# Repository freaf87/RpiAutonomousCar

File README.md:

Rpi Autonomous Car PCB 
====================
This board bring those additional functions below to the Raspberry pi:

	 - Analog Digital Converter with MCP3008 (8)
	 - DC Brushed Motor driver (2) with TB6612FNG
	 - Level converted IOs (5V <-> 3.3V) (8)
     - 16-channel, 12-bit PWM with PCA9685
     - RGB LED (1)
     - Pushbutton (1)

Top                                                                      |  Bottom
:-----------------------------------------------------------------------:|:--------------------------------------------------------------:
  |  

Author: Frederic Afadjigla, 2018

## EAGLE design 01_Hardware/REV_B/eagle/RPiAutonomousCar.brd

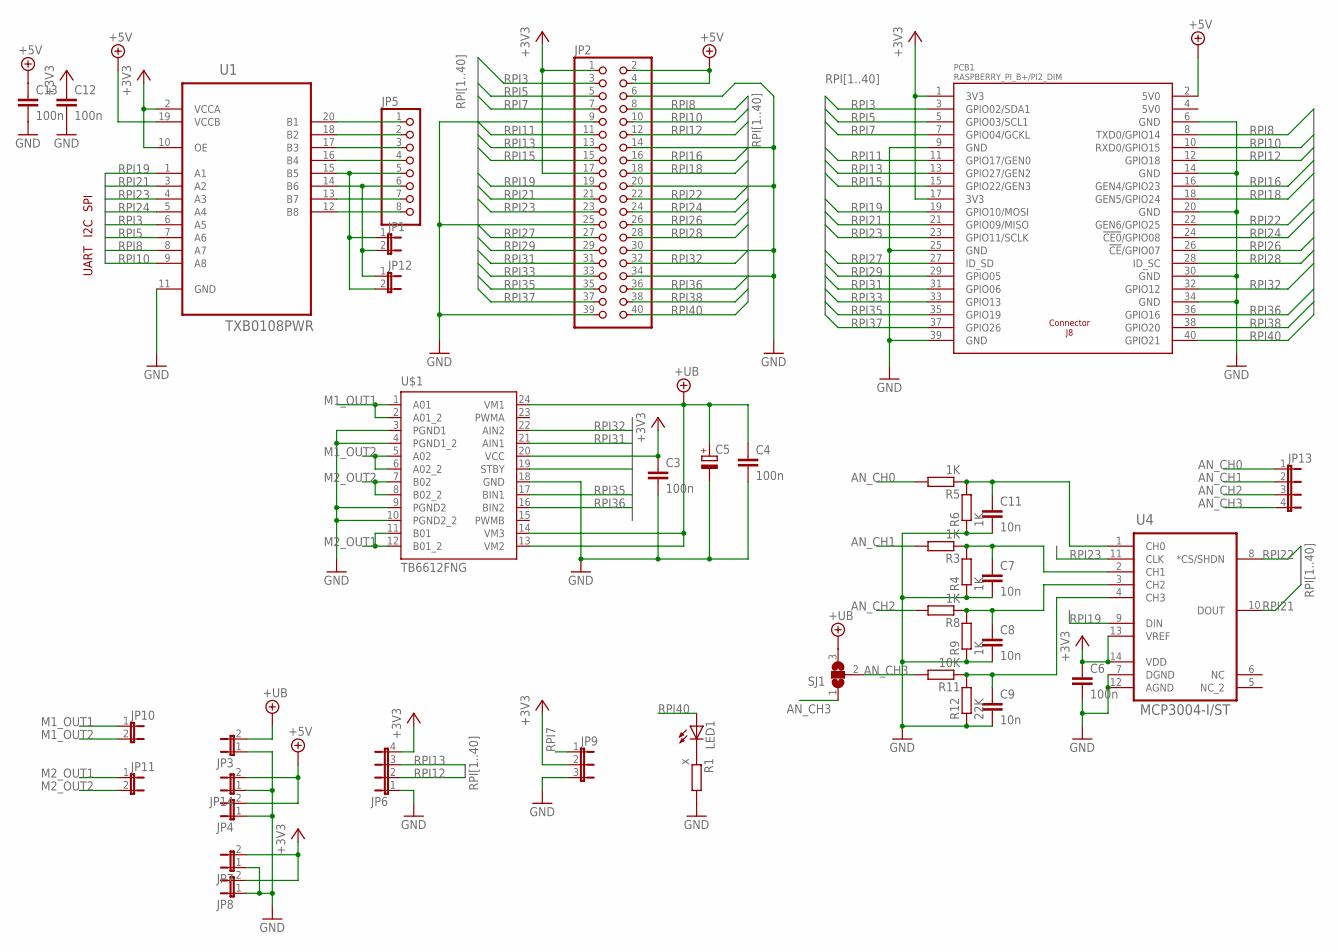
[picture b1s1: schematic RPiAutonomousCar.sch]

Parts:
C3, C4, C6, C12, C13: 100n; C0603
C5: CPOL-EU153CLV-0405; 153CLV-0405
C7, C8, C9, C11: 10n; C0603
JP1, JP3, JP4, JP7, JP8, JP10, JP11, JP12, JP14: JP1E; JP1
JP2: PINHD-2X20; 2X20
JP5: PINHD-1X8; 1X08
JP6, JP13: JP4E; JP4
JP9: JP2E; JP2
LED1: LEDSML0603; SML0603
PCB1: RASPBERRY_PI_B+/PI2_DIM; RASPBERRY_PI_BPLUS_HEADER_ONLY
R1: x; R0603
R3, R4, R5, R6, R8, R9: 1K; R0603
R11: 10K; R0603
R12: 22K; R0603
SJ1: SJ2W; SJ_2
U1: TXB0108PWR; SOP65P640X120-20N
U4: MCP3004-I/ST; SOP65P640X120-14N
U$1: TB6612FNG; SSOP24

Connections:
5V0: PCB1.4 (5V0)
+3V3: C3.1, C6.1, C12.1, JP2.1, JP2.17, JP6.4, JP7.2, JP8.2, JP9.2, PCB1.1 (3V3), PCB1.17 (3V3), U1.2 (VCCA), U1.10 (OE), U4.13 (VREF), U4.14 (VDD), U$1.20 (VCC)
+5V: C13.1, JP2.2, JP2.4, JP4.2, JP14.2, PCB1.2 (5V0), U1.19 (VCCB)
+UB: C4.1, C5.+, JP3.2, SJ1.3, U$1.13 (VM2), U$1.14 (VM3), U$1.24 (VM1)
AN_CH0: JP13.1, R5.2
AN_CH1: JP13.2, R3.2
AN_CH2: JP13.3, R8.2
AN_CH3: JP13.4, R11.2, SJ1.1, SJ1.2
GND: C3.2, C4.2, C5.-, C6.2, C7.2, C8.2, C9.2, C11.2, C12.2, C13.2, JP2.6, JP2.9, JP2.14, JP2.20, JP2.25, JP2.30, JP2.34, JP2.39, JP3.1, JP4.1, JP6.1, JP7.1, JP8.1, JP9.3, JP14.1, PCB1.6 (GND), PCB1.9 (GND), PCB1.14 (GND), PCB1.20 (GND), PCB1.25 (GND), PCB1.30 (GND), PCB1.34 (GND), PCB1.39 (GND), R1.2, R4.1, R6.1, R9.1, R12.1, U1.11 (GND), U4.7 (DGND), U4.12 (AGND), U$1.3 (PGND1), U$1.4 (PGND1_2), U$1.9 (PGND2), U$1.10 (PGND2_2), U$1.18 (GND)
M1_OUT1: JP10.1, U$1.1 (A01), U$1.2 (A01_2)
M1_OUT2: JP10.2, U$1.5 (A02), U$1.6 (A02_2)
M2_OUT1: JP11.1, U$1.11 (B01), U$1.12 (B01_2)
M2_OUT2: JP11.2, U$1.7 (B02), U$1.8 (B02_2)
unnamed: JP5.8, U1.12 (B8)
unnamed: JP5.7, U1.13 (B7)
unnamed: JP1.2, JP5.6, JP12.1, U1.14 (B6)
unnamed: JP5.4, U1.16 (B4)
unnamed: JP5.3, U1.17 (B3)
unnamed: JP5.2, U1.18 (B2)
unnamed: JP5.1, U1.20 (B1)
unnamed: C11.1, R5.1, R6.2, U4.1 (CH0)
unnamed: LED1.C, R1.1
unnamed: C7.1, R3.1, R4.2, U4.2 (CH1)
unnamed: C8.1, R8.1, R9.2, U4.3 (CH2)
unnamed: C9.1, R11.1, R12.2, U4.4 (CH3)
unnamed: JP1.1, JP5.5, JP12.2, U1.15 (B5)
RPI3: JP2.3, PCB1.3 (GPIO02/SDA1), U1.6 (A5)
RPI5: JP2.5, PCB1.5 (GPIO03/SCL1), U1.7 (A6)
RPI7: JP2.7, JP9.1, PCB1.7 (GPIO04/GCKL)
RPI8: JP2.8, PCB1.8 (TXD0/GPIO14), U1.8 (A7)
RPI10: JP2.10, PCB1.10 (RXD0/GPIO15), U1.9 (A8)
RPI11: JP2.11, PCB1.11 (GPIO17/GEN0)
RPI12: JP2.12, JP6.2, PCB1.12 (GPIO18)
RPI13: JP2.13, JP6.3, PCB1.13 (GPIO27/GEN2)
RPI15: JP2.15, PCB1.15 (GPIO22/GEN3)
RPI16: JP2.16, PCB1.16 (GEN4/GPIO23)
RPI18: JP2.18, PCB1.18 (GEN5/GPIO24)
RPI19: JP2.19, PCB1.19 (GPIO10/MOSI), U1.1 (A1), U4.9 (DIN)
RPI21: JP2.21, PCB1.21 (GPIO09/MISO), U1.3 (A2), U4.10 (DOUT)
RPI22: JP2.22, PCB1.22 (GEN6/GPIO25), U4.8 (*CS/SHDN)
RPI23: JP2.23, PCB1.23 (GPIO11/SCLK), U1.4 (A3), U4.11 (CLK)
RPI24: JP2.24, PCB1.24 (!CE0!/GPIO08), U1.5 (A4)
RPI26: JP2.26, PCB1.26 (!CE!/GPIO07)
RPI27: JP2.27, PCB1.27 (ID_SD)
RPI28: JP2.28, PCB1.28 (ID_SC)
RPI29: JP2.29, PCB1.29 (GPIO05)
RPI31: JP2.31, PCB1.31 (GPIO06), U$1.21 (AIN1)
RPI32: JP2.32, PCB1.32 (GPIO12), U$1.22 (AIN2)
RPI33: JP2.33, PCB1.33 (GPIO13)
RPI35: JP2.35, PCB1.35 (GPIO19), U$1.17 (BIN1)
RPI36: JP2.36, PCB1.36 (GPIO16), U$1.16 (BIN2)
RPI37: JP2.37, PCB1.37 (GPIO26)
RPI38: JP2.38, PCB1.38 (GPIO20), U$1.19 (STBY)
RPI40: JP2.40, LED1.A, PCB1.40 (GPIO21)

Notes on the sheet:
SPI
I2C
UART

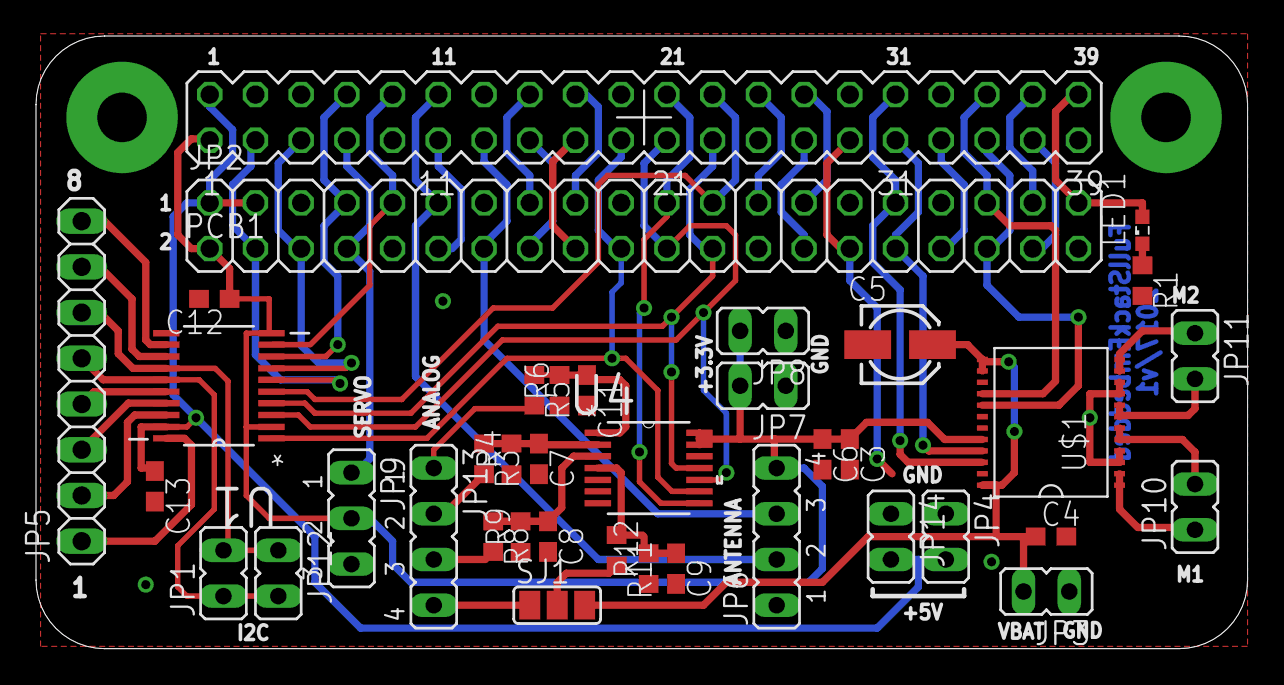
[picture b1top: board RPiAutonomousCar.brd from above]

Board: 2 copper layers, 67.3 x 34.0 mm, 39 parts (0 on the bottom side), 53 nets.

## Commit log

2017-05-01 routing...
2017-05-13 routing
2017-05-26 routing ...
2017-05-29 rounting/Pinout minor changes
2017-05-29 routing almost done
2017-05-30 routing done
2017-06-05 ready for review
2017-06-07 routing done. Ready to order
2017-06-10 Version 1 done
2017-06-11 Hardware Documentation added
2017-06-13 Documenting...
2017-06-17 Restructure Directories
2017-06-18 add cost calculation
2017-06-24 driver HCSR04 LED MCP3004 TB6612FNG added
2017-06-24 moinor corrections
2017-06-24 servo driver added
2017-06-28 add simple autonomous program
2017-07-09 Remote control added
2017-08-05 minor changes
2017-08-18 Docu actualised
2017-09-15 Thread based Line follower added
2017-09-23 Line follower (continued)
2017-10-28 Refactor and add TODOs
2017-10-28 Add test of drive function
2017-10-28 Implement turning
2017-10-29 Add ultrasonic current measurement property
2017-10-29 Add obstacle detection test
2017-10-29 Add curve driving function
2017-10-29 Add option to skip tests
2017-10-30 Hardware PWM support
2017-10-31 Add shebangs, encoding and license headers
2017-10-31 Use new API for autonomous driving
2017-10-31 Use continuous drive mode
2017-10-31 Rename for PEP8
2017-10-31 Perform complete rotation to keep from tangling code in test
2017-10-31 Remove unused file
2017-10-31 Refactor ultrasonic ranger
2017-10-31 Migrate to wiringpi
2017-11-02 Call builtin debug rather than self-made
2017-11-02 Establish connection within Receiver class
2017-11-02 Move connection closing into class
2017-11-02 Have class start thread on its own
2017-11-02 Simplify command sending logic
2017-11-02 Close connection through context manager
2017-11-02 PEP8 and light refactor of LED
2017-11-02 Move GPIO bookkeeping into superclass
2017-11-02 Subclass LED to GPIO_Manager
2017-11-02 Factor distance measurements into properties
2017-11-02 Migrate infrared sensor to subclass GPIO_Manager
2017-11-02 Move hardware modules into their own package
2017-11-04 Use INPUT/OUTPUT constants from wiringpi
2017-11-04 Use __exit__ rather than destroy methods
2017-11-04 Migrate to motor_driver to wiringpi
2017-11-04 Add LED test, reorganize controllers
2017-11-04 Roll code into package
2017-11-04 HW Pwm modifications
2017-11-04 Insert headers, rename files
2017-11-04 Refactor LineFollowers
2017-11-05 Refactor ADC code
2017-11-05 Use Robot in LineFollower
2017-11-05 Use correct constant
2017-11-05 Naming refactor
2017-11-05 Finish renaming
2017-11-05 Further refactoring of TB6612FNG
2017-11-05 Correct typo
2017-11-12 Fix TB6612FNG driver
2017-11-12 Migrate to hardware PWM
2017-11-12 Refactoring
2017-11-12 Add infrared interface to Robot
2017-11-12 Add dependencies
2017-11-12 Simplify LineFollower
2017-11-12 Check for sudo in MotorDriver
2017-11-12 Adjust duty cycle
2017-11-12 typo
2017-11-12 Bugfix
2017-11-12 Adjust Robot's duty cycle
2017-11-12 Use absolute, not relative imports
2017-11-12 Add long description to setup.py
2017-11-12 Business as usual when no obstacle found
2017-11-12 Fix bug in line follower
2017-11-12 Proper exit for LineFollower
2017-11-12 Improve line following
2017-11-12 Finalize remote control
2017-12-03 Pass through non-sudoer error for tests
2017-12-03 Properly register motor driver pins
2018-01-21 (1) Changes from Lome and Ghana (2) Board Revision B started
2018-01-28 Designing RevB
2018-02-04 Work in Progress
2018-02-04 Brd redo due to kicad update
2018-02-25 Set theme jekyll-theme-dinky
2018-04-04 kicad version REVB added
2018-04-22 Routing started
2018-04-23 Reorder
2018-04-24 remaning resistors added to PCA9685 w/ routing
2018-04-30 Routing in progress
2018-05-27 Taster added. routing not done
2018-06-08 Routing done. Ready to be manufactured
2018-06-09 Last Modification: Jumper J5 long pad smd used
2018-08-11 Motor driver updated
2018-08-12 ADC and PWM Driver completed
2018-09-30 REVB-02 implemented. (1) Rpi header mirrored (2) New Switch added (THR) (3) New RGB LED
